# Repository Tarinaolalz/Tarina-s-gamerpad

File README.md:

# Tarina-s-gamerpad
simple wasd keypad with volume control, led lights and a special key
## Design Process
i wanted to make a keyboard that i could use so i thought i should make a wasd keypad that i can use to play games. the process was very long and tiring but it was kinda fun. i thought to add extra stuff like leds, a volume knob and an extra key just because i didnt want it to be basic.

## PCB
here is a picture of my schematics

it didnt take too long for me to put this together since i had the guide to help me out.

here is a picture of my pcb :

i had practiced using kiCAD beforehand so creating the pcb wasnt such a hard process

## Case
i made the case using fusion360 and it took so long and was not hard but my computer kept lagging so it was kind of annoying but i am so glad i had the guide to help out and make the process easier.

here is a picutre of my case:

## BOM
- 5x Cherry MX Switches
- 4x SK6812 MINI LEDS
- 1x XIAO RP2040
- 5x Blank DSA Keycaps
- 1x EC11 Rotary Encoder
- 1x Case (top and base)
- 4x M3x16 Bolt
- 4x M3 heatset

## Overview
this is my first electronics project  and i think i did a decent job idk T_T but it was really challenging but fun to do, a great learning experience and i kinda want to do more.

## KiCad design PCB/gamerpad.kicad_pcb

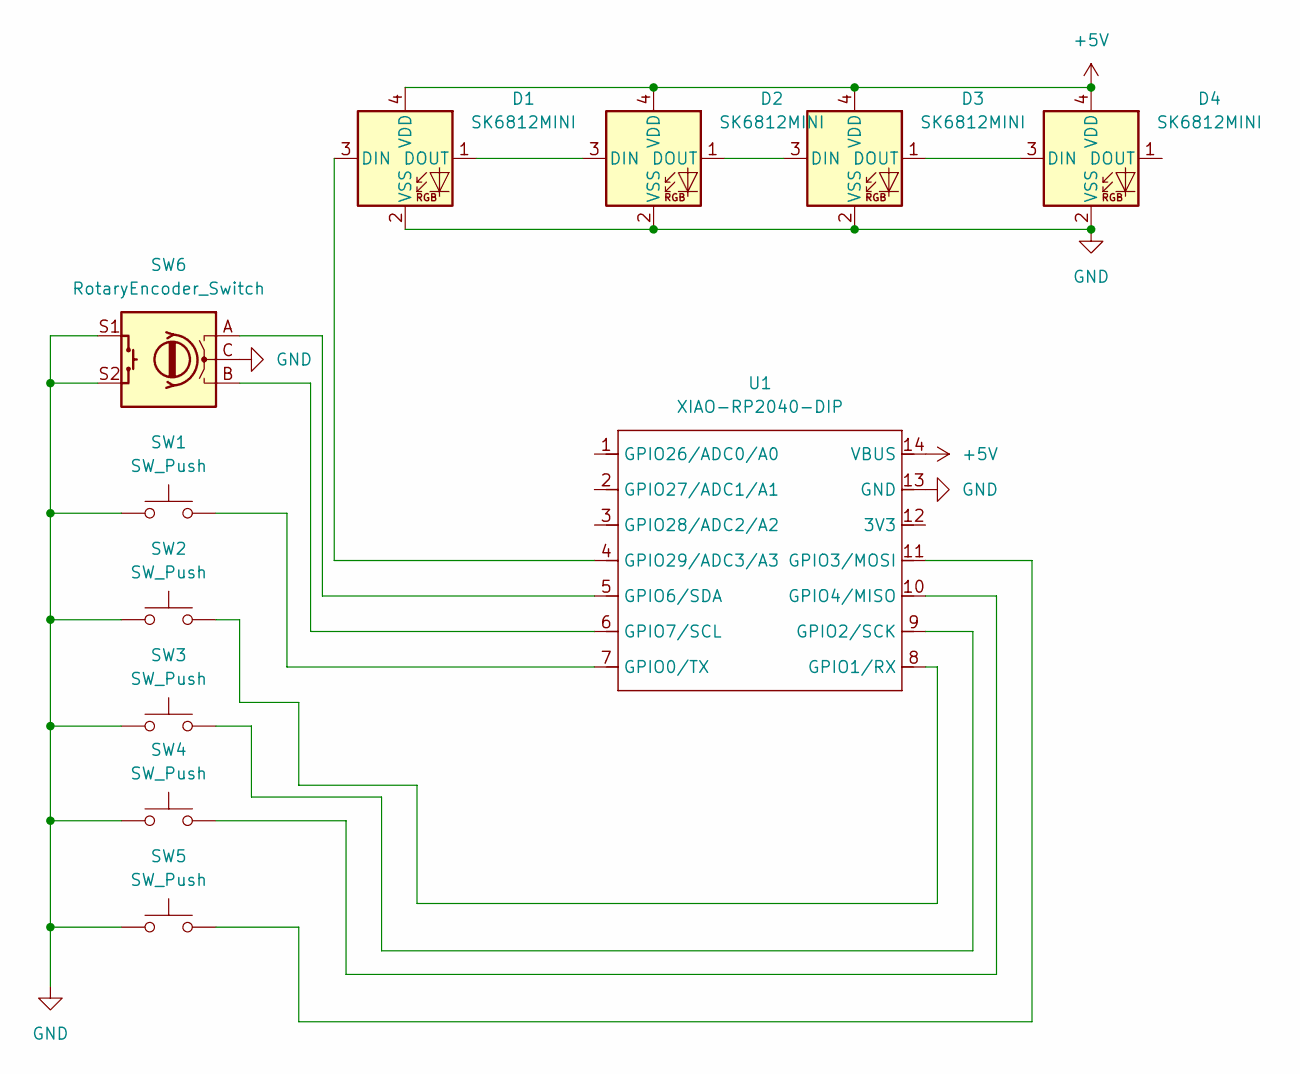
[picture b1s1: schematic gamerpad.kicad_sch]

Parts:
D1, D2, D3, D4: SK6812MINI; LED_SK6812MINI_PLCC4_3.5x3.5mm_P1.75mm
SW1, SW2, SW3, SW4, SW5: SW_Push; SW_Cherry_MX_1.00u_PCB
SW6: RotaryEncoder_Switch; RotaryEncoder_Alps_EC11E-Switch_Vertical_H20mm_CircularMoun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
U1: XIAO-RP2040-DIP

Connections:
+5V: D1.4 (VDD), D2.4 (VDD), D3.4 (VDD), D4.4 (VDD), U1.14 (VBUS)
GND: D1.2 (VSS), D2.2 (VSS), D3.2 (VSS), D4.2 (VSS), SW1.1, SW2.1, SW3.1, SW4.1, SW5.1, SW6.C, SW6.S1, SW6.S2, U1.13 (GND)
unnamed: D1.3 (DIN), U1.4 (GPIO29/ADC3/A3)
unnamed: D1.1 (DOUT), D2.3 (DIN)
unnamed: D2.1 (DOUT), D3.3 (DIN)
unnamed: D3.1 (DOUT), D4.3 (DIN)
unnamed: SW1.2, U1.7 (GPIO0/TX)
unnamed: SW2.2, U1.8 (GPIO1/RX)
unnamed: SW3.2, U1.9 (GPIO2/SCK)
unnamed: SW5.2, U1.11 (GPIO3/MOSI)
unnamed: SW4.2, U1.10 (GPIO4/MISO)
unnamed: SW6.A, U1.5 (GPIO6/SDA)
unnamed: SW6.B, U1.6 (GPIO7/SCL)

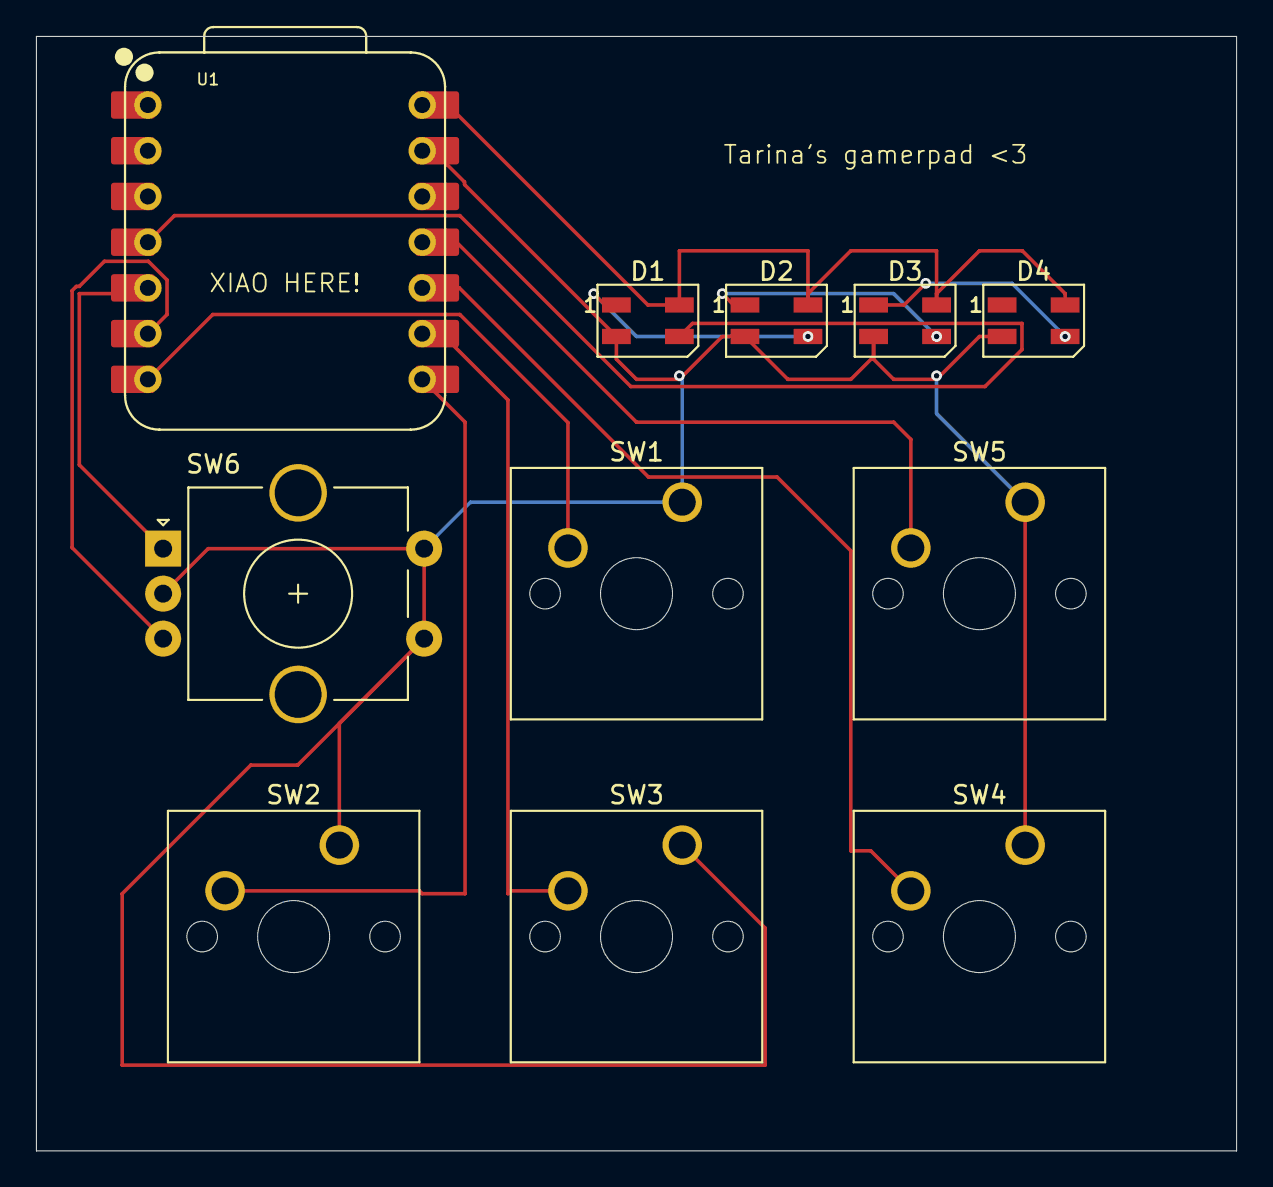
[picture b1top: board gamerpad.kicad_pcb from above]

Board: 2 copper layers, 66.7 x 61.9 mm, 11 parts (0 on the bottom side), 13 nets.

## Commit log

2025-12-30 organised files
